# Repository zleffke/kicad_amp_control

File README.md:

# kicad_amp_control
VTGS SX-Band Ground Station Power Amplifier Control Board

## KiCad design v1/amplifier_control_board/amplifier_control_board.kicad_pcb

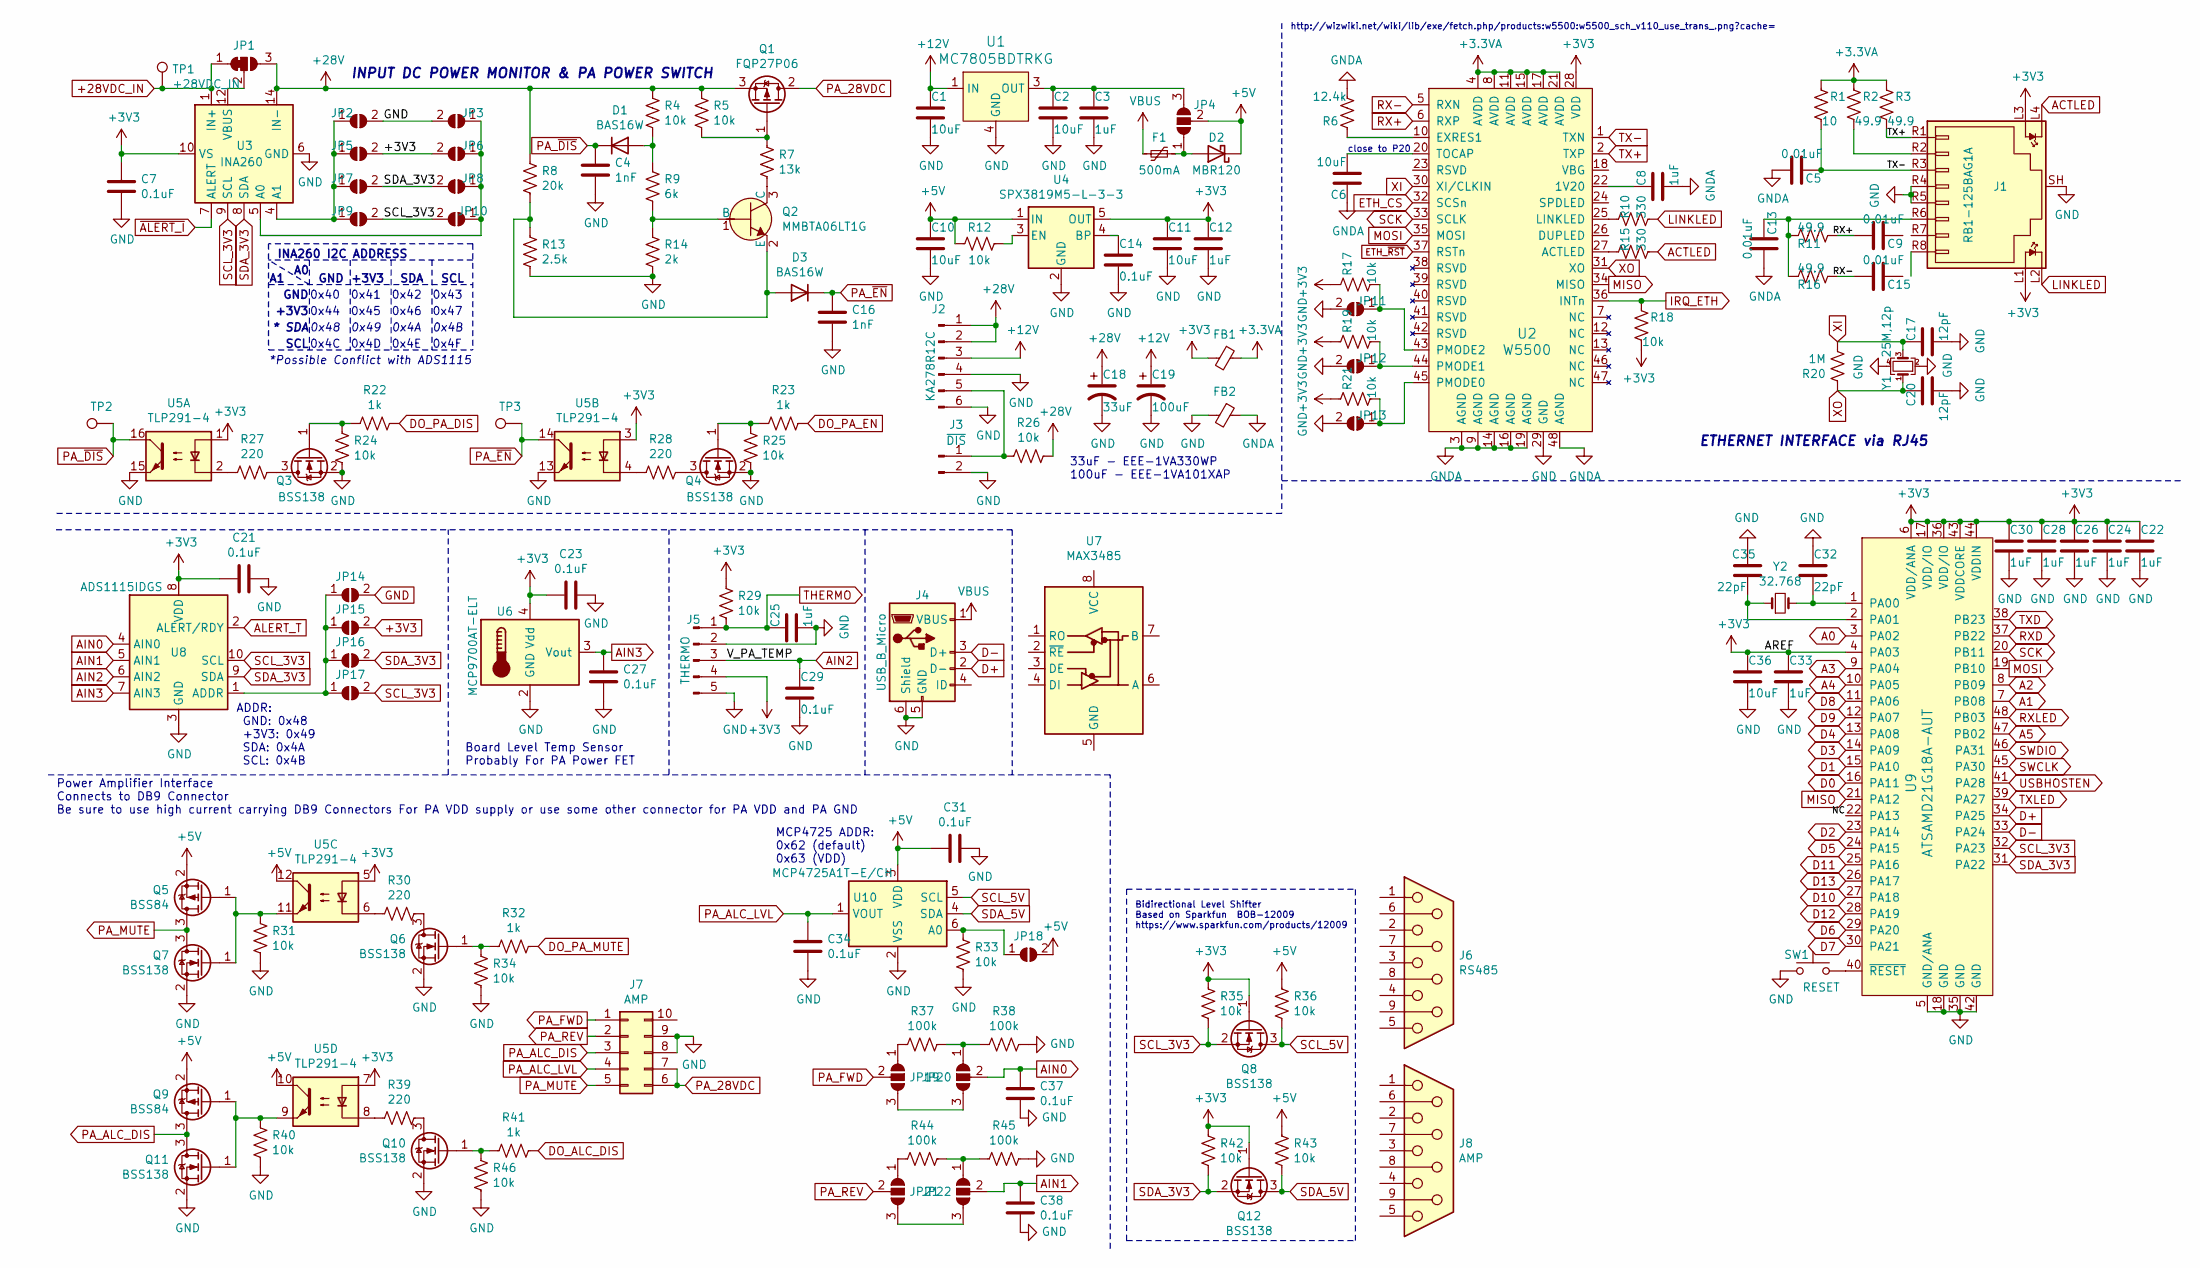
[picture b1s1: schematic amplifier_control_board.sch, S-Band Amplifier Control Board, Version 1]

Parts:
C1, C2, C6, C10, C11, C36: 10uF; 0805
C3, C8, C12, C22, C24, C25, C26, C28, C30, C33: 1uF; 0805
C4, C16: 1nF; 0805
C5, C9, C13, C15: 0.01uF; 0805
C7, C14, C21, C23, C27, C29, C31, C34, C37, C38: 0.1uF; 0805
C17, C20: 12pF; 0805
C18: 33uF; CP_Elec_6.3x5.4
C19: 100uF; CP_Elec_6.3x7.7
C32, C35: 22pF; 0805
D1, D3: BAS16W; SOT-323_SC-70
D2: MBR120; D_SOD-123
F1: 500mA; Fuse_1206_3216Metric
FB1, FB2: Ferrite_Bead_Small; 0805
J1: RB1-125BAG1A; RJ45_Female_RB1-125BAG1A; MPN RB1-125BAG1A; Digi-Key_PN 1278-1011-ND
J2: KA278R12C; PinHeader_1x06_P2.54mm_Vertical
J3: ~DIS; PinHeader_1x02_P2.54mm_Vertical
J4: USB_B_Micro; USB_Micro-B_Wuerth_629105150521_CircularHoles
J5: THERMO; PinHeader_1x05_P2.54mm_Vertical
J6: RS485; DSUB-9_Male_EdgeMount_P2.77mm
J7: AMP; PinHeader_2x05_P2.54mm_Vertical
J8: AMP; DSUB-9_Male_EdgeMount_P2.77mm
JP1: VBUS; SolderJumper-3_P1.3mm_Open_RoundedPad1.0x1.5mm
JP2, JP3, JP5, JP6, JP7, JP8, JP9, JP10: I_ADDR; SolderJumper-2_P1.3mm_Open_TrianglePad1.0x1.5mm
JP4, JP19, JP20, JP21, JP22: FWD1; SolderJumper-3_P1.3mm_Open_RoundedPad1.0x1.5mm_NumberLabels
JP11: PMODE2; SolderJumper-2_P1.3mm_Open_TrianglePad1.0x1.5mm
JP12: PMODE1; SolderJumper-2_P1.3mm_Open_TrianglePad1.0x1.5mm
JP13: PMODE0; SolderJumper-2_P1.3mm_Open_TrianglePad1.0x1.5mm
JP14, JP15, JP16, JP17, JP18: DAC_ADDR; SolderJumper-2_P1.3mm_Open_TrianglePad1.0x1.5mm
Q1: FQP27P06; TO-263-2
Q2: MMBTA06LT1G; SOT-23-3; MPN MMBTA06LT1G; Digi-Key_PN MMBTA06LT1GOSCT-ND
Q3, Q4, Q6, Q7, Q8, Q10, Q11, Q12: BSS138; SOT-23
Q5, Q9: BSS84; SOT-23
R1: 10; 0805
R2, R3, R11, R16: 49.9; 0805
R4, R5, R12, R17, R18, R19, R21, R24, R25, R26, R29, R31, R33, R34, R35, R36, R40, R42, R43, R46: 10k; 0805
R6: 12.4k; 0805
R7: 13k; 0805
R8: 20k; 0805
R9: 6k; 0805
R10, R15: 330; 0805
R13: 2.5k; 0805
R14: 2k; 0805
R20: 1M; 0805
R22, R23, R32, R41: 1k; 0805
R27, R28, R30, R39: 220; 0805
R37, R38, R44, R45: 100k; 0805
SW1: RESET; SW_Push_1P1T_NO_CK_KMR2
TP1: +28VDC_IN; TestPoint_Pad_4.0x4.0mm
TP2, TP3: PA_~DIS; TestPoint_Pad_2.5x2.5mm
U1: MC7805BDTRKG; TO-252-3; MPN MC7805BDTRKG; Digi-Key_PN MC7805BDTRKGOSCT-ND
U2: W5500; LQFP-48_7x7mm_P0.5mm; MPN W5500; Digi-Key_PN 1278-1021-ND
U3: INA260; TSSOP-16_4.4x5mm_P0.65mm
U4: SPX3819M5-L-3-3; SOT-23-5
U5: TLP291-4; SOIC-16_4.55x10.3mm_P1.27mm
U6: MCP9700AT-ELT; SOT-353_SC-70-5
U7: MAX3485; SOIC-8_3.9x4.9mm_P1.27mm
U8: ADS1115IDGS; TSSOP-10_3x3mm_P0.5mm
U9: ATSAMD21G18A-AUT; TQFP-48_7x7mm_P0.5mm; MPN ATSAMD21G18A-AUT; Digi-Key_PN ATSAMD21G18A-AUTCT-ND
U10: MCP4725A1T-E/CH; SOT-23-6
Y1: 25M,12p; Crystal_SMD_Abracon_ABM8G-4Pin_3.2x2.5mm
Y2: 32.768; Crystal_SMD_G8-2Pin_3.2x1.5mm_HandSoldering

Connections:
+3.3VA: FB1.1, R1.1, R2.1, R3.1, U2.4 (AVDD), U2.8 (AVDD), U2.11 (AVDD), U2.15 (AVDD), U2.17 (AVDD), U2.21 (AVDD)
+3V3: C7.1, C11.2, C12.2, C21.2, C22.2, C23.1, C24.2, C26.2, C28.1, C30.2, C33.2, C36.2, FB1.2, J1.L1, J1.L3, J5.4, JP5.2 (B), JP6.2 (B), JP15.2 (B), Q8.1 (G), Q12.1 (G), R17.1, R18.2, R19.1, R21.1, R29.1, R35.1, R42.1, U2.28 (VDD), U3.10 (VS), U4.5 (OUT), U5.1, U5.3, U5.5, U5.7, U6.4 (Vdd), U8.8 (VDD), U9.4 (PA03), U9.6 (VDD/ANA), U9.17 (VDD/IO), U9.36 (VDD/IO), U9.43 (VDDCORE), U9.44 (VDDIN)
+5V: C10.2, C31.2, D2.1 (K), JP4.2 (C), JP18.2 (B), Q5.2 (S), Q9.2 (S), R12.2, R36.1, R43.1, U4.1 (IN), U5.10, U5.12, U10.3 (VDD)
+12V: C1.2, C19.1, J2.3, U1.1 (IN)
+28V: C18.1, J2.1, J2.2, JP1.3 (B), Q1.3 (S), R4.2, R5.2, R8.2, R26.1, U3.14 (IN-), U3.15 (IN-), U3.16 (IN-)
+28VDC_IN: JP1.1 (A), TP1.1, U3.1 (IN+), U3.2 (IN+), U3.3 (IN+)
/NC: U9.22 (PA13)
A0: U9.3 (PA02)
A1: U9.7 (PB08)
A2: U9.8 (PB09)
A3: U9.9 (PA04)
A4: U9.10 (PA05)
A5: U9.47 (PB02)
ACTLED: J1.L4, R15.2
AIN0: C37.2, JP20.2 (C), U8.4 (AIN0)
AIN1: C38.2, JP22.2 (C), U8.5 (AIN1)
AIN2: C29.2, J5.3, U8.6 (AIN2)
AIN3: C27.2, U6.3 (Vout), U8.7 (AIN3)
ALERT_T: U8.2 (ALERT/RDY)
D0: U9.16 (PA11)
D1: U9.15 (PA10)
D2: U9.23 (PA14)
D3: U9.14 (PA09)
D4: U9.13 (PA08)
D5: U9.24 (PA15)
D6: U9.29 (PA20)
D7: U9.30 (PA21)
D8: U9.11 (PA06)
D9: U9.12 (PA07)
D10: U9.27 (PA18)
D11: U9.25 (PA16)
D12: U9.28 (PA19)
D13: U9.26 (PA17)
D+: J4.2 (D-), U9.34 (PA25)
D-: J4.3 (D+), U9.33 (PA24)
DO_ALC_DIS: R41.2
DO_PA_DIS: R22.2
DO_PA_EN: R23.2
DO_PA_MUTE: R32.2
ETH_CS: U2.32 (SCSn)
ETH_~RST: U2.37 (RSTn)
GND: C1.1, C2.1, C3.1, C4.2, C7.2, C10.1, C11.1, C12.1, C14.1, C16.2, C17.1, C18.2, C19.2, C20.1, C21.1, C22.1, C23.2, C24.1, C25.1, C26.1, C27.1, C28.2, C29.1, C30.1, C31.1, C32.2, C33.1, C34.2, C35.2, C36.1, C37.1, C38.1, FB2.2, J1.R4, J1.R5, J1.SH, J2.4, J2.6, J3.2, J4.5 (GND), J4.6 (Shield), J5.2, J5.5, J7.8, J7.9, JP2.2 (B), JP3.2 (B), JP11.2 (B), JP12.2 (B), JP13.2 (B), JP14.2 (B), Q3.2 (S), Q4.2 (S), Q6.2 (S), Q7.2 (S), Q10.2 (S), Q11.2 (S), R13.1, R14.1, R24.1, R25.1, R31.1, R33.2, R34.1, R38.1, R40.1, R45.1, R46.1, SW1.1, U1.4 (GND), U2.29 (GND), U3.6 (GND), U3.11 (GND), U4.2 (GND), U5.13, U5.15, U6.2 (GND), U8.3 (GND), U9.5 (GND/ANA), U9.18 (GND), U9.35 (GND), U9.42 (GND), U10.2 (VSS), Y1.2, Y1.4
GNDA: C5.1, C6.2, C8.1, C13.1, FB2.1, R6.2, U2.3 (AGND), U2.9 (AGND), U2.14 (AGND), U2.16 (AGND), U2.19 (AGND), U2.48 (AGND)
IRQ_ETH: R18.1, U2.36 (INTn)
LINKLED: J1.L2, R10.2
MISO: U2.34 (MISO), U9.21 (PA12)
MOSI: U2.35 (MOSI), U9.19 (PB10)
unnamed: C2.2, C3.2, JP4.3 (B), U1.3 (OUT)
unnamed: C6.1, U2.20 (TOCAP)
unnamed: C8.2, U2.22 (1V20)
unnamed: C13.2, J1.R6, R11.2, R16.2
unnamed: C14.2, U4.4 (BP)
unnamed: C32.1, U9.1 (PA00), Y2.2
unnamed: C35.1, U9.2 (PA01), Y2.1
unnamed: D1.1 (A), R4.1, R9.2
unnamed: D2.2 (A), F1.1, JP4.1 (A)
unnamed: D3.1 (A), Q2.2 (E), R8.1, R13.2
unnamed: J1.R2, R2.2
unnamed: J2.5, J3.1, R26.2
unnamed: JP1.2 (C), U3.12 (VBUS)
unnamed: JP2.1 (A), JP5.1 (A), JP7.1 (A), JP9.1 (A), U3.4 (A1)
unnamed: JP3.1 (A), JP6.1 (A), JP8.1 (A), JP10.1 (A), U3.5 (A0)
unnamed: JP11.1 (A), R17.2, U2.43 (PMODE2)
unnamed: JP12.1 (A), R19.2, U2.44 (PMODE1)
unnamed: JP13.1 (A), R21.2, U2.45 (PMODE0)
unnamed: JP14.1 (A), JP15.1 (A), JP16.1 (A), JP17.1 (A), U8.1 (ADDR)
unnamed: JP18.1 (A), R33.1, U10.6 (A0)
unnamed: JP19.1 (A), R37.2
unnamed: JP19.3 (B), JP20.3 (B)
unnamed: JP20.1 (A), R37.1, R38.2
unnamed: JP21.1 (A), R44.2
unnamed: JP21.3 (B), JP22.3 (B)
unnamed: JP22.1 (A), R44.1, R45.2
unnamed: Q1.1 (G), R5.1, R7.2
unnamed: Q2.1 (B), R9.1, R14.2
unnamed: Q2.3 (C), R7.1
unnamed: Q3.1 (G), R22.1, R24.2
unnamed: Q3.3 (D), R27.1
unnamed: Q4.1 (G), R23.1, R25.2
unnamed: Q4.3 (D), R28.1
unnamed: Q5.1 (G), Q7.1 (G), R31.2, U5.11
unnamed: Q6.1 (G), R32.1, R34.2
unnamed: Q6.3 (D), R30.1
unnamed: Q10.1 (G), R41.1, R46.2
unnamed: Q10.3 (D), R39.1
unnamed: Q9.1 (G), Q11.1 (G), R40.2, U5.9
unnamed: R6.1, U2.10 (EXRES1)
unnamed: R10.1, U2.25 (LINKLED)
unnamed: R12.1, U4.3 (EN)
unnamed: R15.1, U2.27 (ACTLED)
unnamed: R27.2, U5.2
unnamed: R28.2, U5.4
unnamed: R30.2, U5.6
unnamed: R39.2, U5.8
unnamed: SW1.2, U9.40 (~RESET)
PA_28VDC: J7.6, J7.7, Q1.2 (D)
PA_ALC_DIS: J7.3, Q9.3 (D), Q11.3 (D)
PA_ALC_LVL: C34.1, J7.4, U10.1 (VOUT)
PA_FWD: J7.1, JP19.2 (C)
PA_MUTE: J7.5, Q5.3 (D), Q7.3 (D)
PA_REV: J7.2, JP21.2 (C)
PA_~DIS: C4.1, D1.3 (K), TP2.1, U5.16
PA_~EN: C16.1, D3.3 (K), TP3.1, U5.14
RX+: C9.1, R11.1, U2.6 (RXP)
RX-: C15.1, R16.1, U2.5 (RXN)
RXD: U9.37 (PB22)
RXLED: U9.48 (PB03)
SCK: U2.33 (SCLK), U9.20 (PB11)
SCL_3V3: JP9.2 (B), JP10.2 (B), JP17.2 (B), Q8.2 (S), R35.2, U3.9 (SCL), U8.10 (SCL), U9.32 (PA23)
SCL_5V: Q8.3 (D), R36.2, U10.5 (SCL)
SDA_3V3: JP7.2 (B), JP8.2 (B), JP16.2 (B), Q12.2 (S), R42.2, U3.8 (SDA), U8.9 (SDA), U9.31 (PA22)
SDA_5V: Q12.3 (D), R43.2, U10.4 (SDA)
SWCLK: U9.45 (PA30)
SWDIO: U9.46 (PA31)
THERMO: C25.2, J5.1, R29.2
TX+: J1.R1, R3.2, U2.2 (TXP)
TX-: C5.2, J1.R3, R1.2, U2.1 (TXN)
TXD: U9.38 (PB23)
TXLED: U9.39 (PA27)
USBHOSTEN: U9.41 (PA28)
VBUS: F1.2, J4.1 (VBUS)
XI: C17.2, R20.2, U2.30 (XI/CLKIN), Y1.3
XO: C20.2, R20.1, U2.31 (XO), Y1.1
~ALERT_I: U3.7 (ALERT)

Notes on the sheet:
0x41
0x43
GND
+3V3
* SDA
SCL
SDA
0x40
0x42
0x44
0x48
0x4C
0x45
0x49
0x4D
0x46
0x4A
0x4E
0x47
0x4B
0x4F
*Possible Conflict with ADS1115
INA260 I2C ADDRESS
INPUT DC POWER MONITOR & PA POWER SWITCH
33uF - EEE-1VA330WP 100uF - EEE-1VA101XAP
close to P20
ETHERNET INTERFACE via RJ45
Board Level Temp Sensor Probably For PA Power FET
ADDR: GND: 0x48 +3V3: 0x49 SDA: 0x4A SCL: 0x4B
Bidirectional Level Shifter Based on Sparkfun BOB-12009 https://www.sparkfun.com/products/12009
Power Amplifier Interface Connects to DB9 Connector Be sure to use high current carrying DB9 Connectors For PA VDD supply or use some other connector for PA VDD and PA GND
MCP4725 ADDR: 0x62 (default) 0x63 (VDD)
http://wizwiki.net/wiki/lib/exe/fetch.php/products:w5500:w5500_sch_v110_use_trans_.png?cache=

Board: 2 copper layers, 148 parts (0 on the bottom side), 88 nets, no tracks yet.

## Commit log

2021-02-22 initial commit ----not sure of status

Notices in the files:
v1/amplifier_control_board/amplifier_control_board.kicad_pcb:
License: CC BY 4.0
v1/amplifier_control_board/amplifier_control_board.sch:
creativecommons.org/licenses/by/4.0
